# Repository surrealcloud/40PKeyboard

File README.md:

# 40P(%) Keyboard

## Why
Buddy wanted to design a keyboard. I wanted a 40% keyboard. We put our engineering degrees to use and made one. 

I also recently designed a PCB in Altium and learned a lot from the experience, so wanted to take a shot at using KiCad. 
This repo only contains my personal contributions to the project.

## Dependencies
I used [Ruiqi Mao's Guide](https://github.com/ruiqimao/keyboard-pcb-guide?tab=readme-ov-file) as a starting point. 
From there I got the [TMK Symbols](https://github.com/tmk/kicad_lib_tmk), [TMK Footprints](https://github.com/tmk/keyboard_parts.pretty), and [Keebs.Pretty Switches](https://github.com/egladman/keebs.pretty?tab=License-1-ov-file#readme)

## TODO
The board is still missing headers for a microcontroller

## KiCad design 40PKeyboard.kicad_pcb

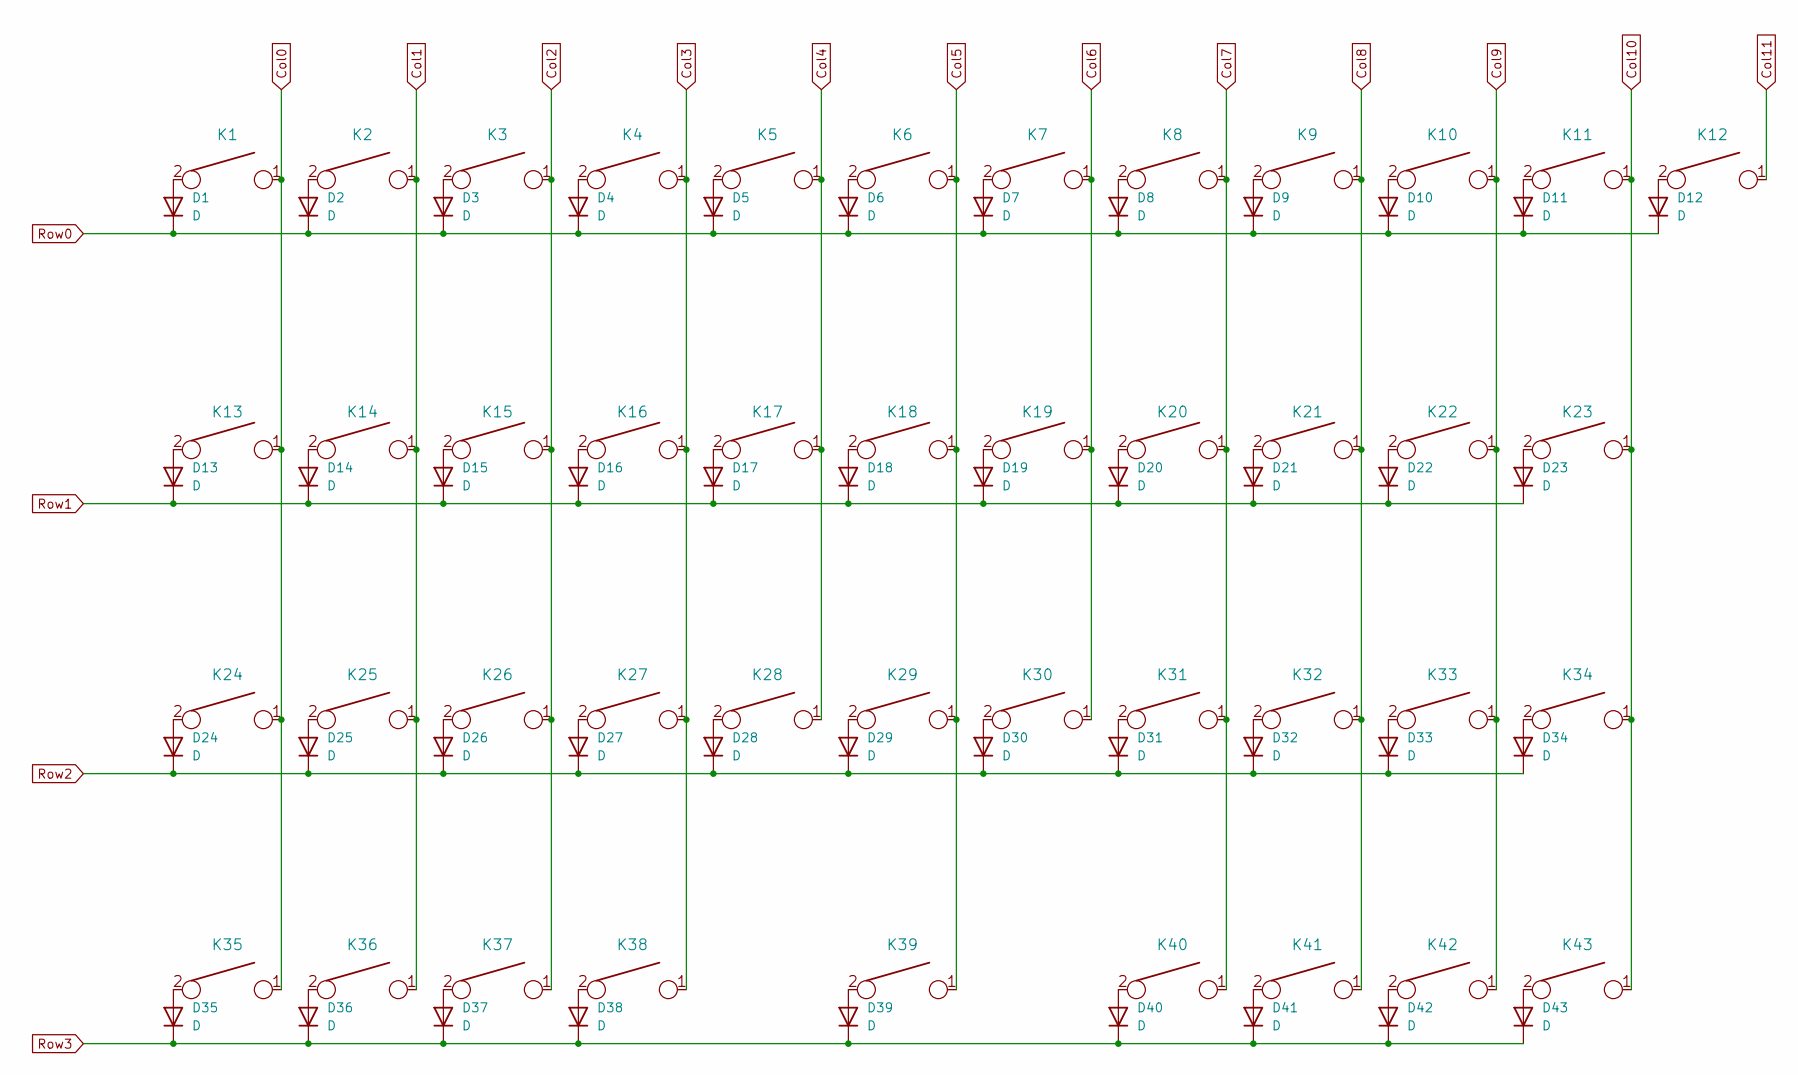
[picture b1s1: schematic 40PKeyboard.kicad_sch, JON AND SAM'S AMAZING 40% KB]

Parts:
D1, D2, D3, D4, D5, D6, D7, D8, D9, D10, D11, D12, D13, D14, D15, D16, D17, D18, D19, D20, D21, D22, D23, D24, D25, D26, D27, D28, D29, D30, D31, D32, D33, D34, D35, D36, D37, D38, D39, D40, D41, D42, D43: D; D_SOD123_axial
K1, K2, K3, K4, K5, K6, K7, K8, K9, K10, K11, K14, K15, K16, K17, K18, K19, K20, K21, K22, K25, K26, K27, K28, K29, K30, K31, K33, K34, K39, K41, K42, K43: KEYSW; Mx_Alps_100
K12, K32: KEYSW; Mx_Alps_175
K13: KEYSW; Mx_Alps_150
K23, K40: KEYSW; Mx_Alps_225
K24: KEYSW; Mx_Alps_200
K35, K36, K37: KEYSW; Mx_Alps_125
K38: KEYSW; Mx_Alps_275

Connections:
Col0: K1.1, K13.1, K24.1, K35.1
Col1: K2.1, K14.1, K25.1, K36.1
Col2: K3.1, K15.1, K26.1, K37.1
Col3: K4.1, K16.1, K27.1, K38.1
Col4: K5.1, K17.1, K28.1
Col5: K6.1, K18.1, K29.1, K39.1
Col6: K7.1, K19.1, K30.1
Col7: K8.1, K20.1, K31.1, K40.1
Col8: K9.1, K21.1, K32.1, K41.1
Col9: K10.1, K22.1, K33.1, K42.1
Col10: K11.1, K23.1, K34.1, K43.1
Col11: K12.1
unnamed: D1.2 (A), K1.2
unnamed: D2.2 (A), K2.2
unnamed: D3.2 (A), K3.2
unnamed: D4.2 (A), K4.2
unnamed: D5.2 (A), K5.2
unnamed: D6.2 (A), K6.2
unnamed: D7.2 (A), K7.2
unnamed: D8.2 (A), K8.2
unnamed: D9.2 (A), K9.2
unnamed: D10.2 (A), K10.2
unnamed: D11.2 (A), K11.2
unnamed: D12.2 (A), K12.2
unnamed: D13.2 (A), K13.2
unnamed: D14.2 (A), K14.2
unnamed: D15.2 (A), K15.2
unnamed: D16.2 (A), K16.2
unnamed: D17.2 (A), K17.2
unnamed: D18.2 (A), K18.2
unnamed: D19.2 (A), K19.2
unnamed: D20.2 (A), K20.2
unnamed: D21.2 (A), K21.2
unnamed: D22.2 (A), K22.2
unnamed: D23.2 (A), K23.2
unnamed: D24.2 (A), K24.2
unnamed: D25.2 (A), K25.2
unnamed: D26.2 (A), K26.2
unnamed: D27.2 (A), K27.2
unnamed: D28.2 (A), K28.2
unnamed: D29.2 (A), K29.2
unnamed: D30.2 (A), K30.2
unnamed: D31.2 (A), K31.2
unnamed: D32.2 (A), K32.2
unnamed: D33.2 (A), K33.2
unnamed: D34.2 (A), K34.2
unnamed: D35.2 (A), K35.2
unnamed: D36.2 (A), K36.2
unnamed: D37.2 (A), K37.2
unnamed: D38.2 (A), K38.2
unnamed: D39.2 (A), K39.2
unnamed: D40.2 (A), K40.2
unnamed: D41.2 (A), K41.2
unnamed: D42.2 (A), K42.2
unnamed: D43.2 (A), K43.2
Row0: D1.1 (K), D2.1 (K), D3.1 (K), D4.1 (K), D5.1 (K), D6.1 (K), D7.1 (K), D8.1 (K), D9.1 (K), D10.1 (K), D11.1 (K), D12.1 (K)
Row1: D13.1 (K), D14.1 (K), D15.1 (K), D16.1 (K), D17.1 (K), D18.1 (K), D19.1 (K), D20.1 (K), D21.1 (K), D22.1 (K), D23.1 (K)
Row2: D24.1 (K), D25.1 (K), D26.1 (K), D27.1 (K), D28.1 (K), D29.1 (K), D30.1 (K), D31.1 (K), D32.1 (K), D33.1 (K), D34.1 (K)
Row3: D35.1 (K), D36.1 (K), D37.1 (K), D38.1 (K), D39.1 (K), D40.1 (K), D41.1 (K), D42.1 (K), D43.1 (K)

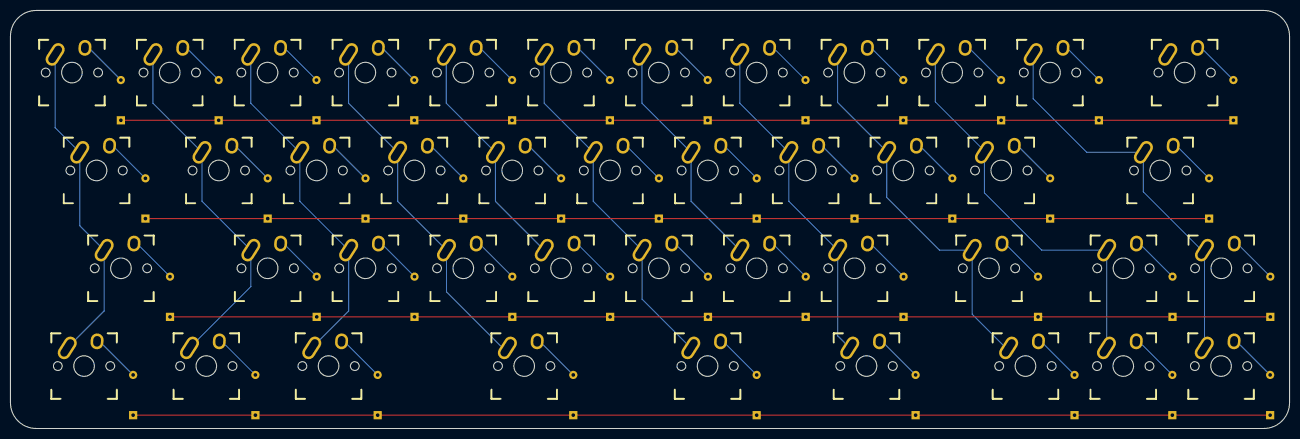
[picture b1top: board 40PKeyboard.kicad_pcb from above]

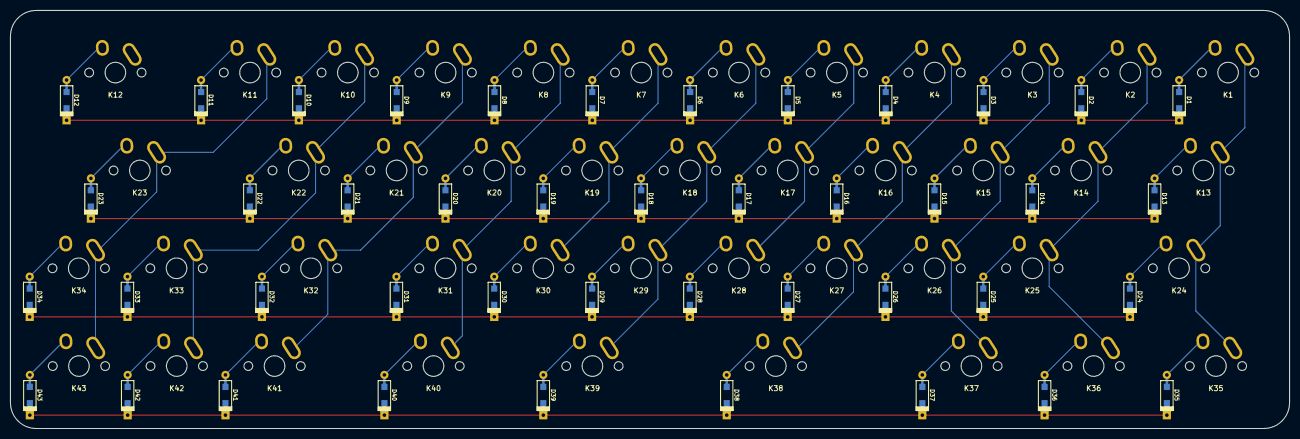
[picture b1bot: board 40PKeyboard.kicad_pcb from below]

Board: 2 copper layers, 247.9 x 81.0 mm, 86 parts (43 on the bottom side), 58 nets.

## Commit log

2024-07-22 Added gitignore
2024-07-22 Added KiCad files
2024-07-22 Removed gitignore files
2024-07-22 Added gitignore file
